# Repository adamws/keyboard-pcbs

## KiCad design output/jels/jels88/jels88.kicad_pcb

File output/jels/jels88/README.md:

## jels/jels88

[layout](jels88-kle.json) - [PCB](jels88.kicad_pcb)

{:loading="lazy"}

[Open in keyboard-layout-editor](http://www.keyboard-layout-editor.com/##@@_x:3.25&c=#777777;&=1,0&_x:0.25&c=#cccccc;&=1,1&=0,1&=0,2&=1,2&_x:0.25&c=#aaaaaa;&=1,3&=0,3&=0,4&=1,4&_x:0.25&c=#cccccc;&=1,5&=0,5&=0,6&=1,6&_x:0.25;&=1,7&_x:0.25&c=#aaaaaa;&=0,7&=0,8&=1,8;&@_x:3.25&y:0.5&c=#cccccc;&=2,0&=2,1&=3,1&=3,2&=2,2&=2,3&=3,3&=3,4&=2,4&=2,5&=3,5&=3,6&=2,6&_c=#aaaaaa&w:2;&=2,7%0A%0A%0A0,0&_x:0.25;&=4,7&=4,8&=2,8;&@_x:3.25&w:1.5;&=5,0&_c=#cccccc;&=5,1&=4,1&=4,2&=5,2&=5,3&=4,3&=4,4&=5,4&=5,5&=4,5&=4,6&=5,6&_w:1.5;&=6,7%0A%0A%0A3,0&_x:0.25&c=#aaaaaa;&=3,7&=3,8&=5,8;&@_x:3.25&w:1.75;&=6,0&_c=#cccccc;&=6,1&=7,1&=7,2&=6,2&=6,3&=7,3&=7,4&=6,4&=6,5&=7,5&=7,6&_c=#777777&w:2.25;&=6,6%0A%0A%0A3,0;&@_x:3.25&c=#aaaaaa&w:2.25;&=9,0%0A%0A%0A1,0&_c=#cccccc;&=8,1&=8,2&=9,2&=9,3&=8,3&=8,4&=9,4&=9,5&=8,5&=8,6&_c=#aaaaaa&w:2.75;&=9,6%0A%0A%0A2,0&_x:1.25;&=8,7;&@_x:3.25&w:1.25;&=10,0%0A%0A%0A4,0&_w:1.25;&=10,1%0A%0A%0A4,0&_w:1.25;&=11,1%0A%0A%0A4,0&_c=#cccccc&w:6.25;&=11,3%0A%0A%0A4,0&_c=#aaaaaa&w:1.25;&=10,5%0A%0A%0A4,0&_w:1.25;&=10,6%0A%0A%0A4,0&_w:1.25;&=11,6%0A%0A%0A4,0&_w:1.25;&=11,7%0A%0A%0A4,0&_x:0.25;&=10,7&=10,8&=8,8;&@_x:23.25&y:-5.0&c=#cccccc;&=2,7%0A%0A%0A0,1&=5,7%0A%0A%0A0,1;&@_x:24.0&c=#aaaaaa&w:1.25&h:2&w2:1.5&h2:1&x2:-0.25;&=6,7%0A%0A%0A3,1;&@_x:23.0&c=#cccccc;&=6,6%0A%0A%0A3,1;&@_c=#aaaaaa&w:1.25;&=9,0%0A%0A%0A1,1&_c=#cccccc;&=9,1%0A%0A%0A1,1&_x:20.25&c=#aaaaaa&w:1.75;&=9,6%0A%0A%0A2,1&=9,7%0A%0A%0A2,1;&@_x:3.25&y:1.0&w:1.5;&=10,0%0A%0A%0A4,1&=10,1%0A%0A%0A4,1&_w:1.5;&=11,1%0A%0A%0A4,1&_c=#cccccc&w:7;&=11,3%0A%0A%0A4,1&_c=#aaaaaa&w:1.5;&=10,6%0A%0A%0A4,1&=11,6%0A%0A%0A4,1&_w:1.5;&=11,7%0A%0A%0A4,1;&@_x:3.25&w:1.5;&=10,0%0A%0A%0A4,2&=10,1%0A%0A%0A4,2&_c=#cccccc&w:10;&=11,3%0A%0A%0A4,2&_c=#aaaaaa;&=11,6%0A%0A%0A4,2&_w:1.5;&=11,7%0A%0A%0A4,2;&@_x:3.25&w:1.5;&=10,0%0A%0A%0A4,3&_d:true;&=%0A%0A%0A4,3&_w:1.5;&=11,1%0A%0A%0A4,3&_c=#cccccc&w:7;&=11,3%0A%0A%0A4,3&_c=#aaaaaa&w:1.5;&=10,6%0A%0A%0A4,3&_d:true;&=%0A%0A%0A4,3&_w:1.5;&=11,7%0A%0A%0A4,3;&@_x:3.25&w:1.5;&=10,0%0A%0A%0A4,4&_d:true;&=%0A%0A%0A4,4&_c=#cccccc&w:10;&=11,3%0A%0A%0A4,4&_c=#aaaaaa&d:true;&=%0A%0A%0A4,4&_w:1.5;&=11,7%0A%0A%0A4,4)

{:loading="lazy"}

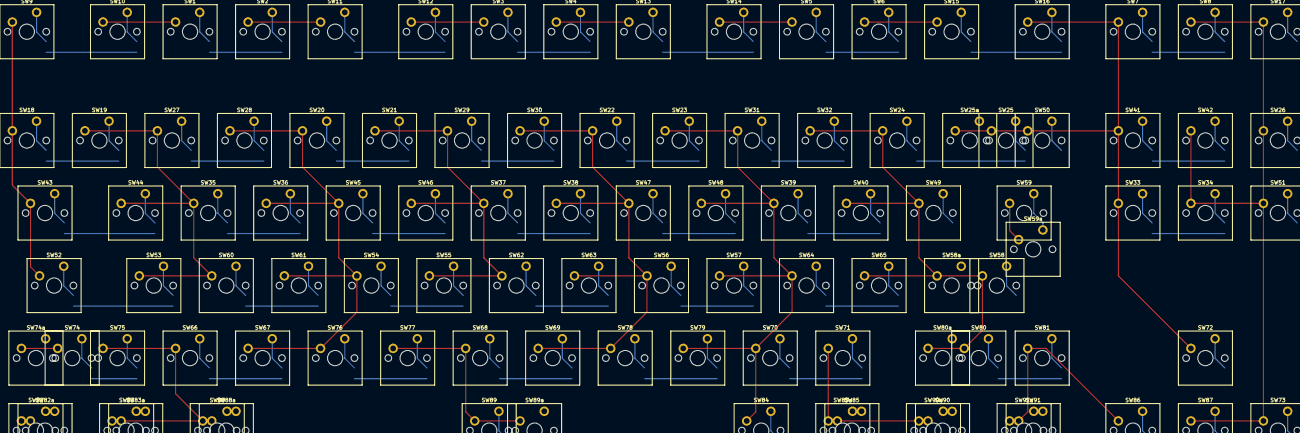
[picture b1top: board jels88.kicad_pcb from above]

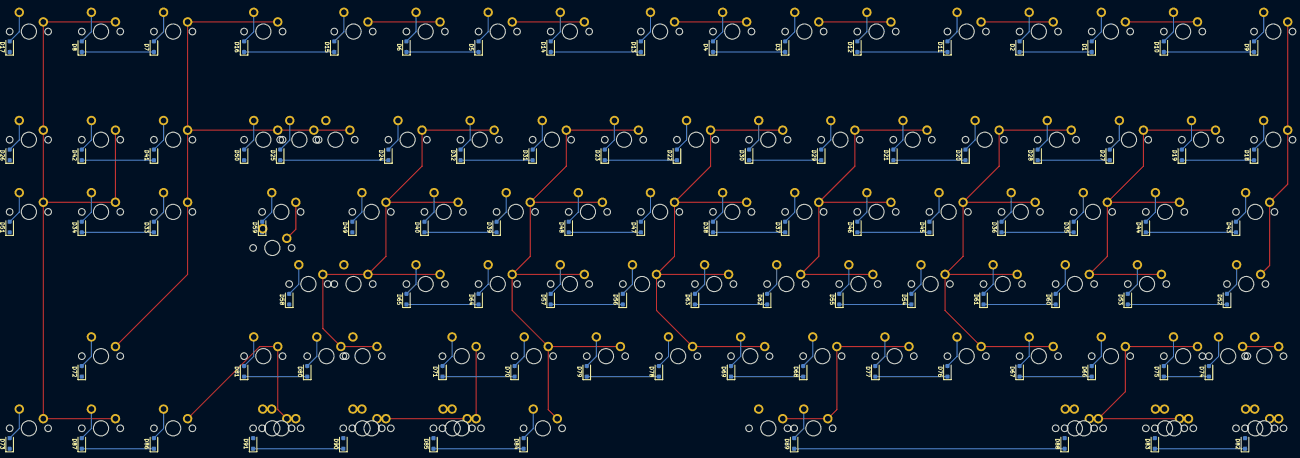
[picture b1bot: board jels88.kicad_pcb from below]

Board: 2 copper layers, 194 parts (91 on the bottom side), 112 nets.

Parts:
D1, D2, D3, D4, D5, D6, D7, D8, D9, D10, D11, D12, D13, D14, D15, D16, D17, D18, D19, D20, D21, D22, D23, D24, D25, D26, D27, D28, D29, D30, D31, D32, D33, D34, D35, D36, D37, D38, D39, D40, D41, D42, D43, D44, D45, D46, D47, D48, D49, D50, D51, D52, D53, D54, D55, D56, D57, D58, D59, D60, D61, D62, D63, D64, D65, D66, D67, D68, D69, D70, D71, D72, D73, D74, D75, D76, D77, D78, D79, D80, D81, D82, D83, D84, D85, D86, D87, D88, D89, D90, D91: D_SOD-123F
SW1, SW2, SW3, SW4, SW5, SW6, SW7, SW8, SW9, SW10, SW11, SW12, SW13, SW14, SW15, SW16, SW17, SW18, SW19, SW20, SW21, SW22, SW23, SW24, SW25, SW25a, SW26, SW27, SW28, SW29, SW30, SW31, SW32, SW33, SW34, SW35, SW36, SW37, SW38, SW39, SW40, SW41, SW42, SW43, SW44, SW45, SW46, SW47, SW48, SW49, SW50, SW51, SW52, SW53, SW54, SW55, SW56, SW57, SW58, SW58a, SW59, SW59a, SW60, SW61, SW62, SW63, SW64, SW65, SW66, SW67, SW68, SW69, SW70, SW71, SW72, SW73, SW74, SW74a, SW75, SW76, SW77, SW78, SW79, SW80, SW80a, SW81, SW82, SW82a, SW83, SW83a, SW84, SW85, SW85a, SW86, SW87, SW88, SW88a, SW89, SW89a, SW90, SW90a, SW91, SW91a: SW_Cherry_MX_PCB_1.00u

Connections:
COL0: SW9.1, SW18.1, SW43.1, SW52.1, SW74.1, SW74a.1, SW82.1, SW82a.1
COL1: SW1.1, SW10.1, SW19.1, SW27.1, SW35.1, SW44.1, SW53.1, SW60.1, SW66.1, SW75.1, SW83.1, SW83a.1, SW88.1, SW88a.1
COL2: SW2.1, SW11.1, SW20.1, SW28.1, SW36.1, SW45.1, SW54.1, SW61.1, SW67.1, SW76.1
COL3: SW3.1, SW12.1, SW21.1, SW29.1, SW37.1, SW46.1, SW55.1, SW62.1, SW68.1, SW77.1, SW89.1, SW89a.1
COL4: SW4.1, SW13.1, SW22.1, SW30.1, SW38.1, SW47.1, SW56.1, SW63.1, SW69.1, SW78.1
COL5: SW5.1, SW14.1, SW23.1, SW31.1, SW39.1, SW48.1, SW57.1, SW64.1, SW70.1, SW79.1, SW84.1
COL6: SW6.1, SW15.1, SW24.1, SW32.1, SW40.1, SW49.1, SW58.1, SW58a.1, SW65.1, SW71.1, SW80.1, SW80a.1, SW85.1, SW85a.1, SW90.1, SW90a.1
COL7: SW7.1, SW16.1, SW25.1, SW25a.1, SW33.1, SW41.1, SW50.1, SW59.1, SW59a.1, SW72.1, SW81.1, SW86.1, SW91.1, SW91a.1
COL8: SW8.1, SW17.1, SW26.1, SW34.1, SW42.1, SW51.1, SW73.1, SW87.1
unnamed: D1.2, SW1.2
unnamed: D2.2, SW2.2
unnamed: D3.2, SW3.2
unnamed: D4.2, SW4.2
unnamed: D5.2, SW5.2
unnamed: D6.2, SW6.2
unnamed: D7.2, SW7.2
unnamed: D8.2, SW8.2
unnamed: D9.2, SW9.2
unnamed: D10.2, SW10.2
unnamed: D11.2, SW11.2
unnamed: D12.2, SW12.2
unnamed: D13.2, SW13.2
unnamed: D14.2, SW14.2
unnamed: D15.2, SW15.2
unnamed: D16.2, SW16.2
unnamed: D17.2, SW17.2
unnamed: D18.2, SW18.2
unnamed: D19.2, SW19.2
unnamed: D20.2, SW20.2
unnamed: D21.2, SW21.2
unnamed: D22.2, SW22.2
unnamed: D23.2, SW23.2
unnamed: D24.2, SW24.2
unnamed: D25.2, SW25.2, SW25a.2
unnamed: D26.2, SW26.2
unnamed: D27.2, SW27.2
unnamed: D28.2, SW28.2
unnamed: D29.2, SW29.2
unnamed: D30.2, SW30.2
unnamed: D31.2, SW31.2
unnamed: D32.2, SW32.2
unnamed: D33.2, SW33.2
unnamed: D34.2, SW34.2
unnamed: D35.2, SW35.2
unnamed: D36.2, SW36.2
unnamed: D37.2, SW37.2
unnamed: D38.2, SW38.2
unnamed: D39.2, SW39.2
unnamed: D40.2, SW40.2
unnamed: D41.2, SW41.2
unnamed: D42.2, SW42.2
unnamed: D43.2, SW43.2
unnamed: D44.2, SW44.2
unnamed: D45.2, SW45.2
unnamed: D46.2, SW46.2
unnamed: D47.2, SW47.2
unnamed: D48.2, SW48.2
unnamed: D49.2, SW49.2
unnamed: D50.2, SW50.2
unnamed: D51.2, SW51.2
unnamed: D52.2, SW52.2
unnamed: D53.2, SW53.2
unnamed: D54.2, SW54.2
unnamed: D55.2, SW55.2
unnamed: D56.2, SW56.2
unnamed: D57.2, SW57.2
unnamed: D58.2, SW58.2, SW58a.2
unnamed: D59.2, SW59.2, SW59a.2
unnamed: D60.2, SW60.2
unnamed: D61.2, SW61.2
unnamed: D62.2, SW62.2
unnamed: D63.2, SW63.2
unnamed: D64.2, SW64.2
unnamed: D65.2, SW65.2
unnamed: D66.2, SW66.2
unnamed: D67.2, SW67.2
unnamed: D68.2, SW68.2
unnamed: D69.2, SW69.2
unnamed: D70.2, SW70.2
unnamed: D71.2, SW71.2
unnamed: D72.2, SW72.2
unnamed: D73.2, SW73.2
unnamed: D74.2, SW74.2, SW74a.2
unnamed: D75.2, SW75.2
unnamed: D76.2, SW76.2
unnamed: D77.2, SW77.2
unnamed: D78.2, SW78.2
unnamed: D79.2, SW79.2
unnamed: D80.2, SW80.2, SW80a.2
unnamed: D81.2, SW81.2
unnamed: D82.2, SW82.2, SW82a.2
unnamed: D83.2, SW83.2, SW83a.2
unnamed: D84.2, SW84.2
unnamed: D85.2, SW85.2, SW85a.2
unnamed: D86.2, SW86.2
unnamed: D87.2, SW87.2
unnamed: D88.2, SW88.2, SW88a.2
unnamed: D89.2, SW89.2, SW89a.2
unnamed: D90.2, SW90.2, SW90a.2
unnamed: D91.2, SW91.2, SW91a.2
ROW0: D1.1, D2.1, D3.1, D4.1, D5.1, D6.1, D7.1, D8.1
ROW1: D9.1, D10.1, D11.1, D12.1, D13.1, D14.1, D15.1, D16.1, D17.1
ROW2: D18.1, D19.1, D20.1, D21.1, D22.1, D23.1, D24.1, D25.1, D26.1
ROW3: D27.1, D28.1, D29.1, D30.1, D31.1, D32.1, D33.1, D34.1
ROW4: D35.1, D36.1, D37.1, D38.1, D39.1, D40.1, D41.1, D42.1
ROW5: D43.1, D44.1, D45.1, D46.1, D47.1, D48.1, D49.1, D50.1, D51.1
ROW6: D52.1, D53.1, D54.1, D55.1, D56.1, D57.1, D58.1, D59.1
ROW7: D60.1, D61.1, D62.1, D63.1, D64.1, D65.1
ROW8: D66.1, D67.1, D68.1, D69.1, D70.1, D71.1, D72.1, D73.1
ROW9: D74.1, D75.1, D76.1, D77.1, D78.1, D79.1, D80.1, D81.1
ROW10: D82.1, D83.1, D84.1, D85.1, D86.1, D87.1
ROW11: D88.1, D89.1, D90.1, D91.1
